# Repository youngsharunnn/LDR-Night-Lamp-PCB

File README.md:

# LDR Night Lamp PCB

A PCB design project for an **LDR (Light Dependent Resistor) based Automatic Night Lamp** created using **KiCad 9**. The circuit automatically switches an LED on in low-light conditions and turns it off when sufficient ambient light is available.

This repository documents the complete PCB design workflow from schematic capture to PCB layout and manufacturing-ready files.

---

## Features

* Automatic light detection using an LDR
* 9V battery powered
* Through-hole components
* Front and back silkscreen graphics
* Ground copper pour
* ERC and DRC verified

---

## Project Overview

The circuit uses an **LDR** and a resistor to create a voltage divider that senses ambient light. An **NPN transistor** acts as a switch to control the LED.

### Operation

#### Bright Environment

* LDR resistance is low.
* The transistor remains OFF.
* LED remains OFF.

#### Dark Environment

* LDR resistance increases.
* The transistor turns ON.
* LED turns ON automatically.

---

## Repository Structure

```text
LDR-Night-Lamp-PCB/
│
├── docs/
│   ├── images/                          # Project screenshots used in the README
│   └── tutorials/                       # Project guides and workflow documentation
│
├── kicad/
│   └── LDR_Night_Lamp/
│       ├── LDR_Night_Lamp.kicad_pro
│       ├── LDR_Night_Lamp.kicad_sch
│       └── LDR_Night_Lamp.kicad_pcb
│
├── Production/
│   ├── BOM/
│   ├── gerber_and_drill
│   ├── pdf/
│   ├── position/
│   └── STEP/
│
├── README.md
└── .gitignore
```

---

## Hardware Used

| Component              |    Quantity |
| --------------------   | ----------: |
| LDR                    |           1 |
| LED                    |           1 |
| NPN Transistor         |           1 |
| Resistors(100kΩ,470Ω)  |     1 x each|
| 9V Battery Connector   |           1 |

---

## Design Verification

Before releasing the PCB:

* ✔ Electrical Rules Check (ERC)
* ✔ Design Rules Check (DRC)
* ✔ Footprint assignment completed
* ✔ PCB routing completed
* ✔ Ground copper pour added
* ✔ Front and back silkscreen finalized

---

## Documentation

The `docs/` folder contains project documentation and visual assets.

* **images/** – Screenshots of the schematic, PCB layout, and 3D views used throughout this README.
* **tutorials/** – Markdown guides documenting the complete KiCad design workflow, Git/GitHub version control process, and manufacturing file generation.

---

## Screenshots

### Schematic

### PCB Layout

### 3D Top View

### 3D Bottom View

### 3D Front View

### 3D Side View

---

## Manufacturing Files

The `Production/` directory contains all files required for PCB fabrication, assembly, and project documentation.

| Folder                | Description                                                                                        |
| --------------------- | -------------------------------------------------------------------------------------------------- |
| **BOM/**              | Bill of Materials (CSV) listing all components required to assemble the PCB.                       |
| **gerber_and_drill/** | Gerber files, drill files, and Gerber job file used by PCB manufacturers for board fabrication.    |
| **PDF/**              | Exported schematic and PCB layout PDFs for documentation, design review, and printing.             |
| **position/**         | Pick-and-Place (PnP) file containing component positions and rotations for automated PCB assembly. |
| **STEP/**             | 3D STEP model of the assembled PCB for mechanical verification and enclosure design.               |

---

## Release

The first stable release of the project is available as **v1.0.0 – Initial Production Release**.

This release contains all files required for PCB fabrication, assembly, and documentation.

### Included Assets

* Gerber & Drill files (`LDR_Night_Lamp_Gerbers_v1.0.0.zip`)
* Bill of Materials (BOM)
* Pick-and-Place (PnP) file
* Schematic PDF
* PCB Layout PDF
* 3D STEP model

Download the latest release from the repository's **Releases** page to access the complete manufacturing package.

---

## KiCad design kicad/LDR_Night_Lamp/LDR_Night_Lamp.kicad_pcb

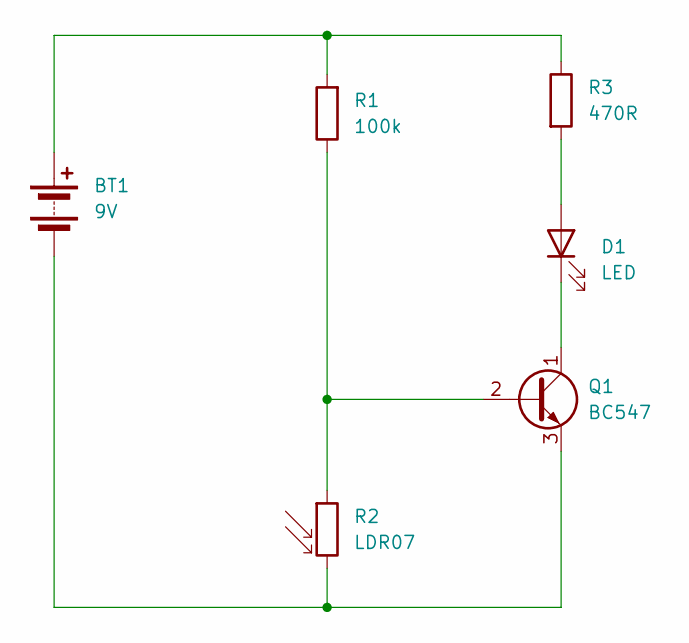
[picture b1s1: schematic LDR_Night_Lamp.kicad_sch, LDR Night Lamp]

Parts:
BT1: 9V; BatteryHolder_MPD_BA9VPC_1xPP3
D1: LED; LED_D5.0mm
Q1: BC547; TO-92_Inline
R1: 100k; R_Axial_DIN0207_L6.3mm_D2.5mm_P15.24mm_Horizontal
R2: LDR07; R_LDR_5.1x4.3mm_P3.4mm_Vertical
R3: 470R; R_Axial_DIN0207_L6.3mm_D2.5mm_P15.24mm_Horizontal

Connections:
unnamed: BT1.1 (+), R1.2, R3.1
unnamed: BT1.2 (-), Q1.3 (E), R2.2
unnamed: D1.2 (A), R3.2
unnamed: D1.1 (K), Q1.1 (C)
unnamed: Q1.2 (B), R1.1, R2.1

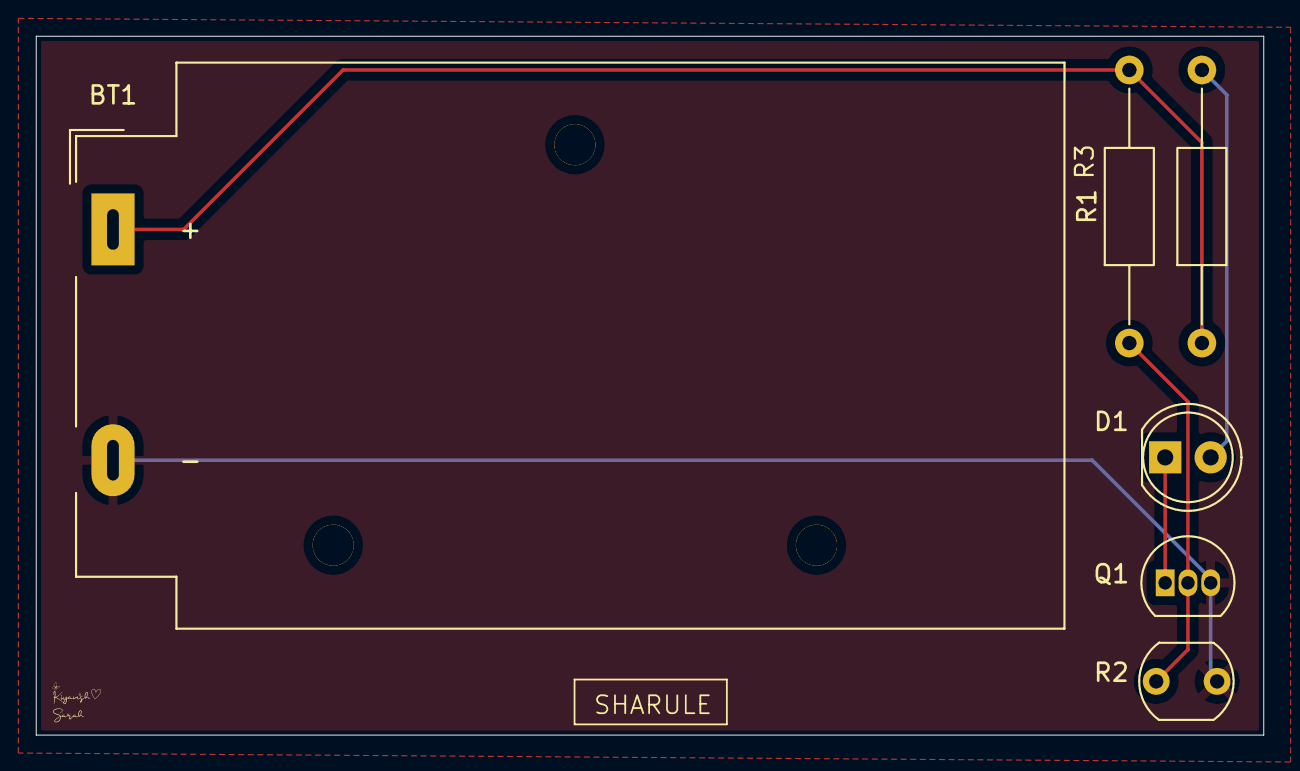
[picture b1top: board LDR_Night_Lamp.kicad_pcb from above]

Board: 2 copper layers, 68.5 x 39.0 mm, 6 parts (0 on the bottom side), 5 nets.

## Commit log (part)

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2026-05-03 chore: initial project structure
2026-05-03 chore: added gitignore for KiCad temp files
2026-05-14 chore: updated gitignore for KiCad autosave files
2026-05-14 fix: removed KiCad autosave files from tracking
2026-05-14 feat: completed initial schematic
